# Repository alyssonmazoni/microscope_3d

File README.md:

# microscope_3d
Firmware and instructions for a 3d microscope design based in Arduino.

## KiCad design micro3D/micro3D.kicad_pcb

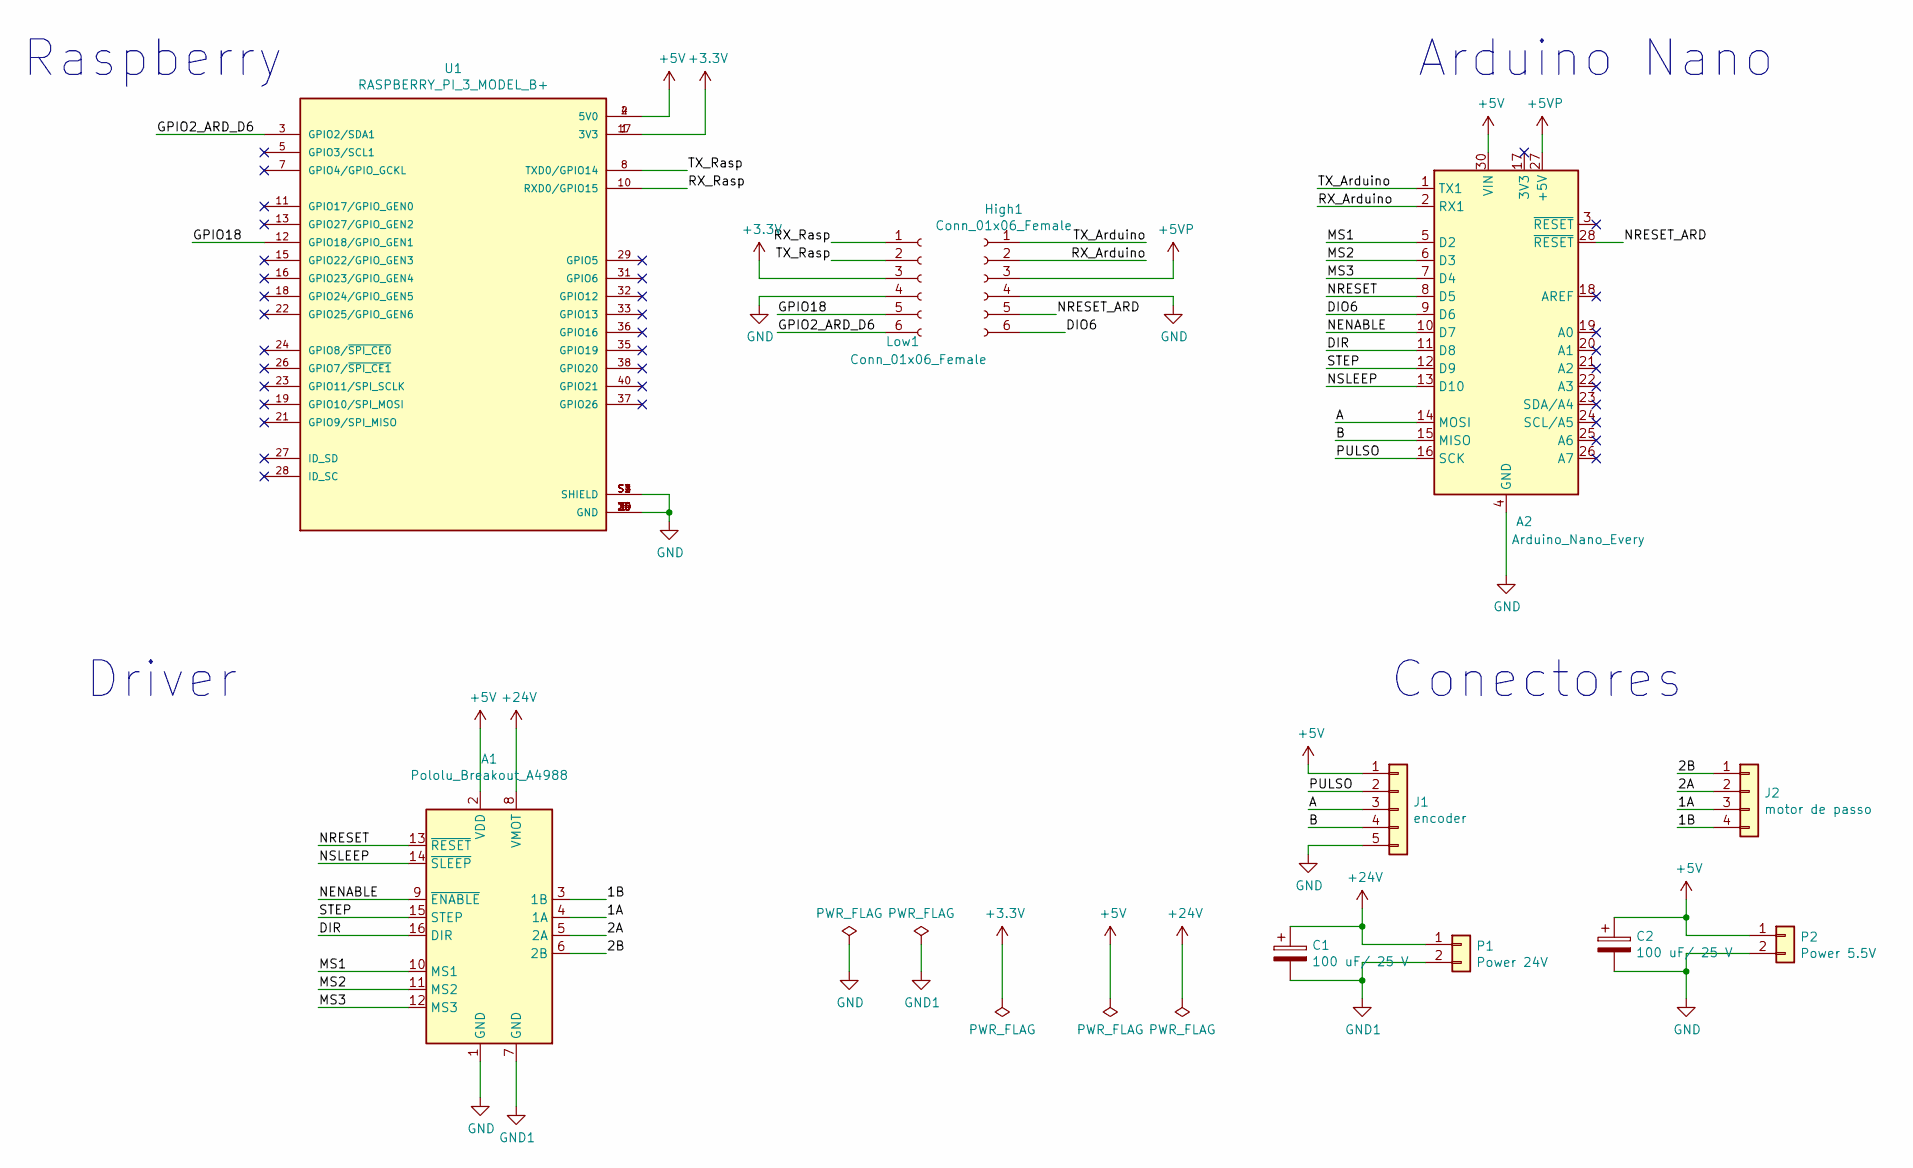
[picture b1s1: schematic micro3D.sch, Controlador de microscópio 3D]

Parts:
A1: Pololu_Breakout_A4988; Pololu_Breakout-16_15.2x20.3mm
A2: Arduino_Nano_Every; Arduino_Nano
C1, C2: 100 uF/ 25 V; C_Radial_D6.3mm_H7.0mm_P2.50mm
High1: Conn_01x06_Female; PinSocket_1x06_P2.54mm_Vertical
J1: encoder; PinHeader_1x05_P2.54mm_Vertical
J2: motor de passo; PinHeader_1x04_P2.54mm_Vertical
Low1: Conn_01x06_Female; PinSocket_1x06_P2.54mm_Vertical
P1: Power 24V; TerminalBlock_Phoenix_MKDS-1,5-2-5.08_1x02_P5.08mm_Horizont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
P2: Power 5.5V; TerminalBlock_Phoenix_MKDS-1,5-2-5.08_1x02_P5.08mm_Horizont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
U1: RASPBERRY_PI_3_MODEL_B+; MODULE_RASPBERRY_PI_3_MODEL_B+; PARTREV 1.0

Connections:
+3V3: Low1.3, U1.1 (3V3), U1.17 (3V3)
+5V: A1.2 (VDD), A2.30 (VIN), C2.1, J1.1, P2.1, U1.2 (5V0), U1.4 (5V0)
+5VP: A2.27 (+5V), High1.3
+24V: A1.8 (VMOT), C1.1, P1.1
/1A: A1.4 (1A), J2.3
/1B: A1.3 (1B), J2.4
/2A: A1.5 (2A), J2.2
/2B: A1.6 (2B), J2.1
/A: A2.14 (MOSI), J1.3
/B: A2.15 (MISO), J1.4
/DIO6: A2.9 (D6), High1.6
/DIR: A1.16 (DIR), A2.11 (D8)
/GPIO2_ARD_D6: Low1.6, U1.3 (GPIO2/SDA1)
/GPIO18: Low1.5, U1.12 (GPIO18/GPIO_GEN1)
/MS1: A1.10 (MS1), A2.5 (D2)
/MS2: A1.11 (MS2), A2.6 (D3)
/MS3: A1.12 (MS3), A2.7 (D4)
/NENABLE: A1.9 (~ENABLE), A2.10 (D7)
/NRESET: A1.13 (~RESET), A2.8 (D5)
/NRESET_ARD: A2.28 (~RESET), High1.5
/NSLEEP: A1.14 (~SLEEP), A2.13 (D10)
/PULSO: A2.16 (SCK), J1.2
/RX_Arduino: A2.2 (RX1), High1.2
/RX_Rasp: Low1.1, U1.10 (RXD0/GPIO15)
/STEP: A1.15 (STEP), A2.12 (D9)
/TX_Arduino: A2.1 (TX1), High1.1
/TX_Rasp: Low1.2, U1.8 (TXD0/GPIO14)
GND: A1.1 (GND), A2.4 (GND), A2.29 (GND), C2.2, High1.4, J1.5, Low1.4, P2.2, U1.6 (GND), U1.9 (GND), U1.14 (GND), U1.20 (GND), U1.25 (GND), U1.30 (GND), U1.34 (GND), U1.39 (GND), U1.S1 (SHIELD), U1.S2 (SHIELD), U1.S3 (SHIELD), U1.S4 (SHIELD)
GND1: A1.7 (GND), C1.2, P1.2

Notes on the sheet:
Raspberry
Arduino Nano
Driver
Conectores

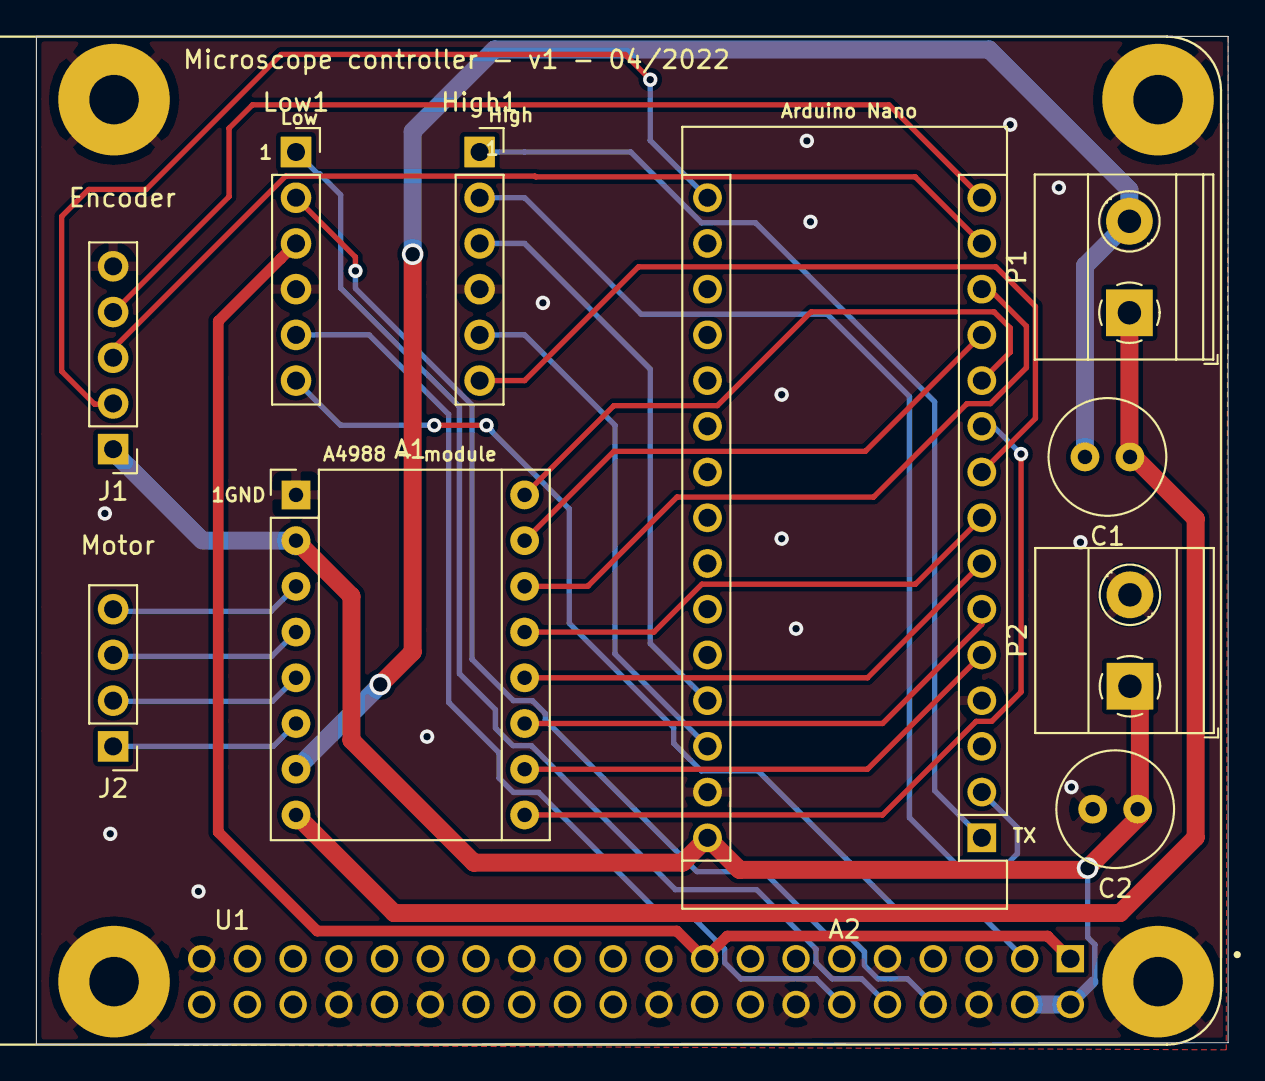
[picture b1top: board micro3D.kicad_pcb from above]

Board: 2 copper layers, 66.2 x 56.0 mm, 11 parts (0 on the bottom side), 29 nets.

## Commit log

2022-11-30 Hardware initial commit.
